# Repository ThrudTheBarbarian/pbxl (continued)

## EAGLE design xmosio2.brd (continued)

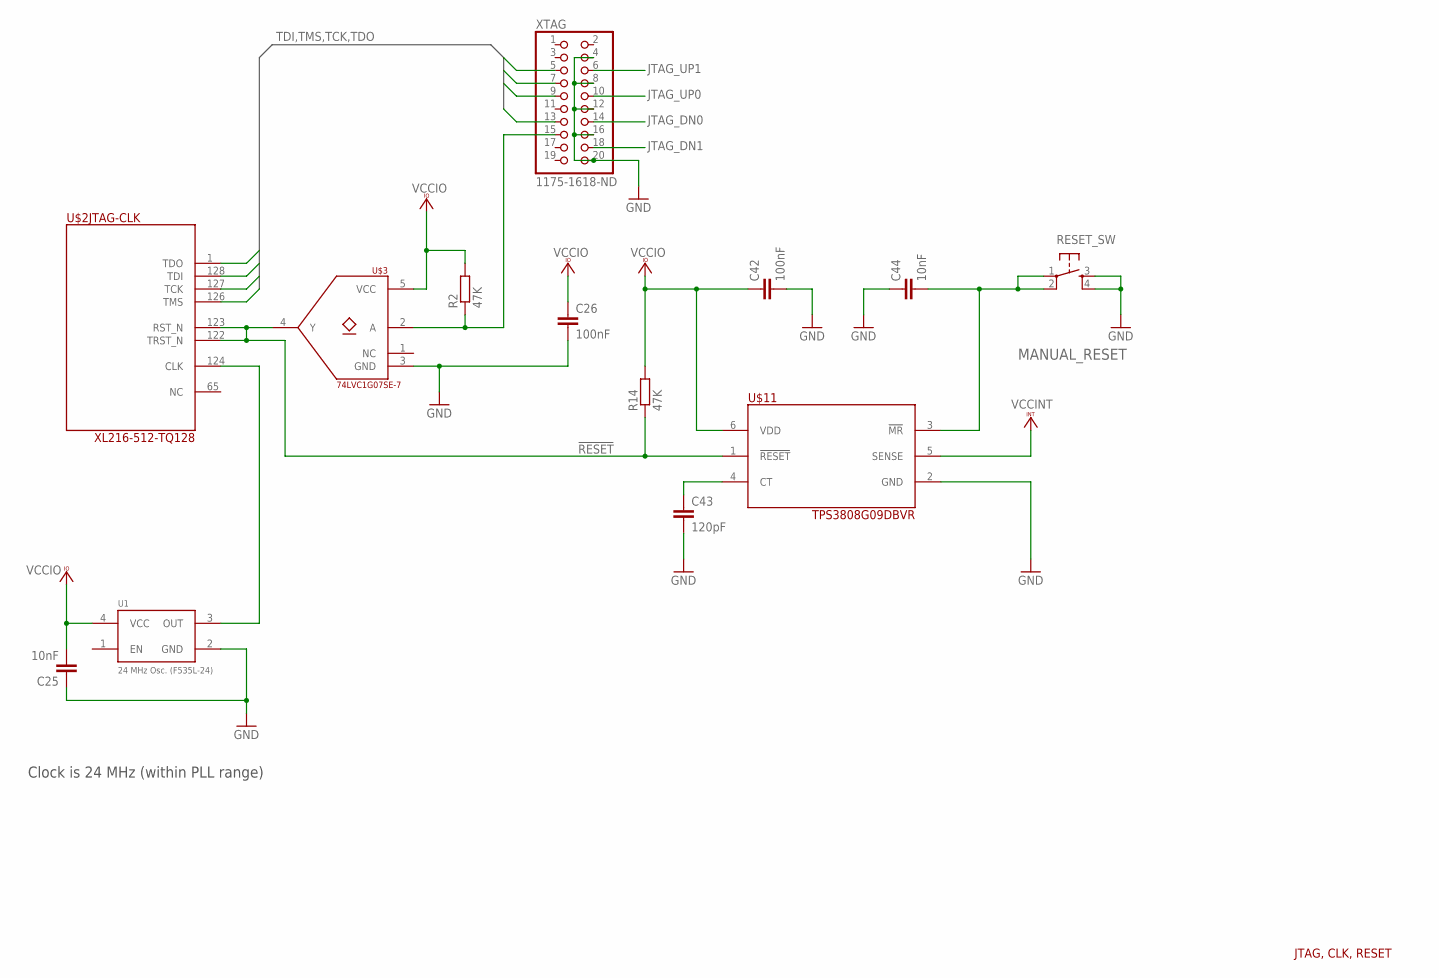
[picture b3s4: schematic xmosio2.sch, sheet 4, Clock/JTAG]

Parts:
C25, C44: 10nF; C0603
C26, C42: 100nF; C0603
C43: 120pF; C0603
R2, R14: 47K; R0603
RESET_SW: MANUAL_RESET; TACTILE-PTH
U1: 24 MHz Osc. (F535L-24); CRYSTAL-OSC-SMD-5X3
U$2: XL216-512-TQ128; TQFP128
U$3: 74LVC1G07SE-7; SOT23-5
U$11: TPS3808G09DBVR; SOT23-6
XTAG: 1175-1618-ND; 2X10/90

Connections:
!RESET!: R14.1, U$2.122 (TRST_N), U$2.123 (RST_N), U$3.4 (Y), U$11.1 (!RESET!)
GND: C25.1, C26.2, C42.2, C43.2, C44.1, RESET_SW.3, RESET_SW.4, U1.2 (GND), U$3.3 (GND), U$11.2 (GND), XTAG.4, XTAG.8, XTAG.12, XTAG.16, XTAG.20; also elsewhere on the board
JTAG_DN0: XTAG.14; also elsewhere on the board
JTAG_DN1: XTAG.18; also elsewhere on the board
JTAG_UP0: XTAG.10; also elsewhere on the board
JTAG_UP1: XTAG.6; also elsewhere on the board
unnamed: U1.3 (OUT), U$2.124 (CLK)
unnamed: R2.1, U$3.2 (A), XTAG.15
unnamed: C43.1, U$11.4 (CT)
unnamed: C44.2, RESET_SW.1, RESET_SW.2, U$11.3 (!MR!)
TCK: U$2.127 (TCK), XTAG.9
TDI: U$2.128 (TDI), XTAG.5
TDO: U$2.1 (TDO), XTAG.13
TMS: U$2.126 (TMS), XTAG.7
VCCINT: U$11.5 (SENSE); also elsewhere on the board
VCCIO: C25.2, C26.1, C42.1, R2.2, R14.2, U1.4 (VCC), U$3.5 (VCC), U$11.6 (VDD); also elsewhere on the board

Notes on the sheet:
JTAG, CLK, RESET
Clock is 24 MHz (within PLL range)

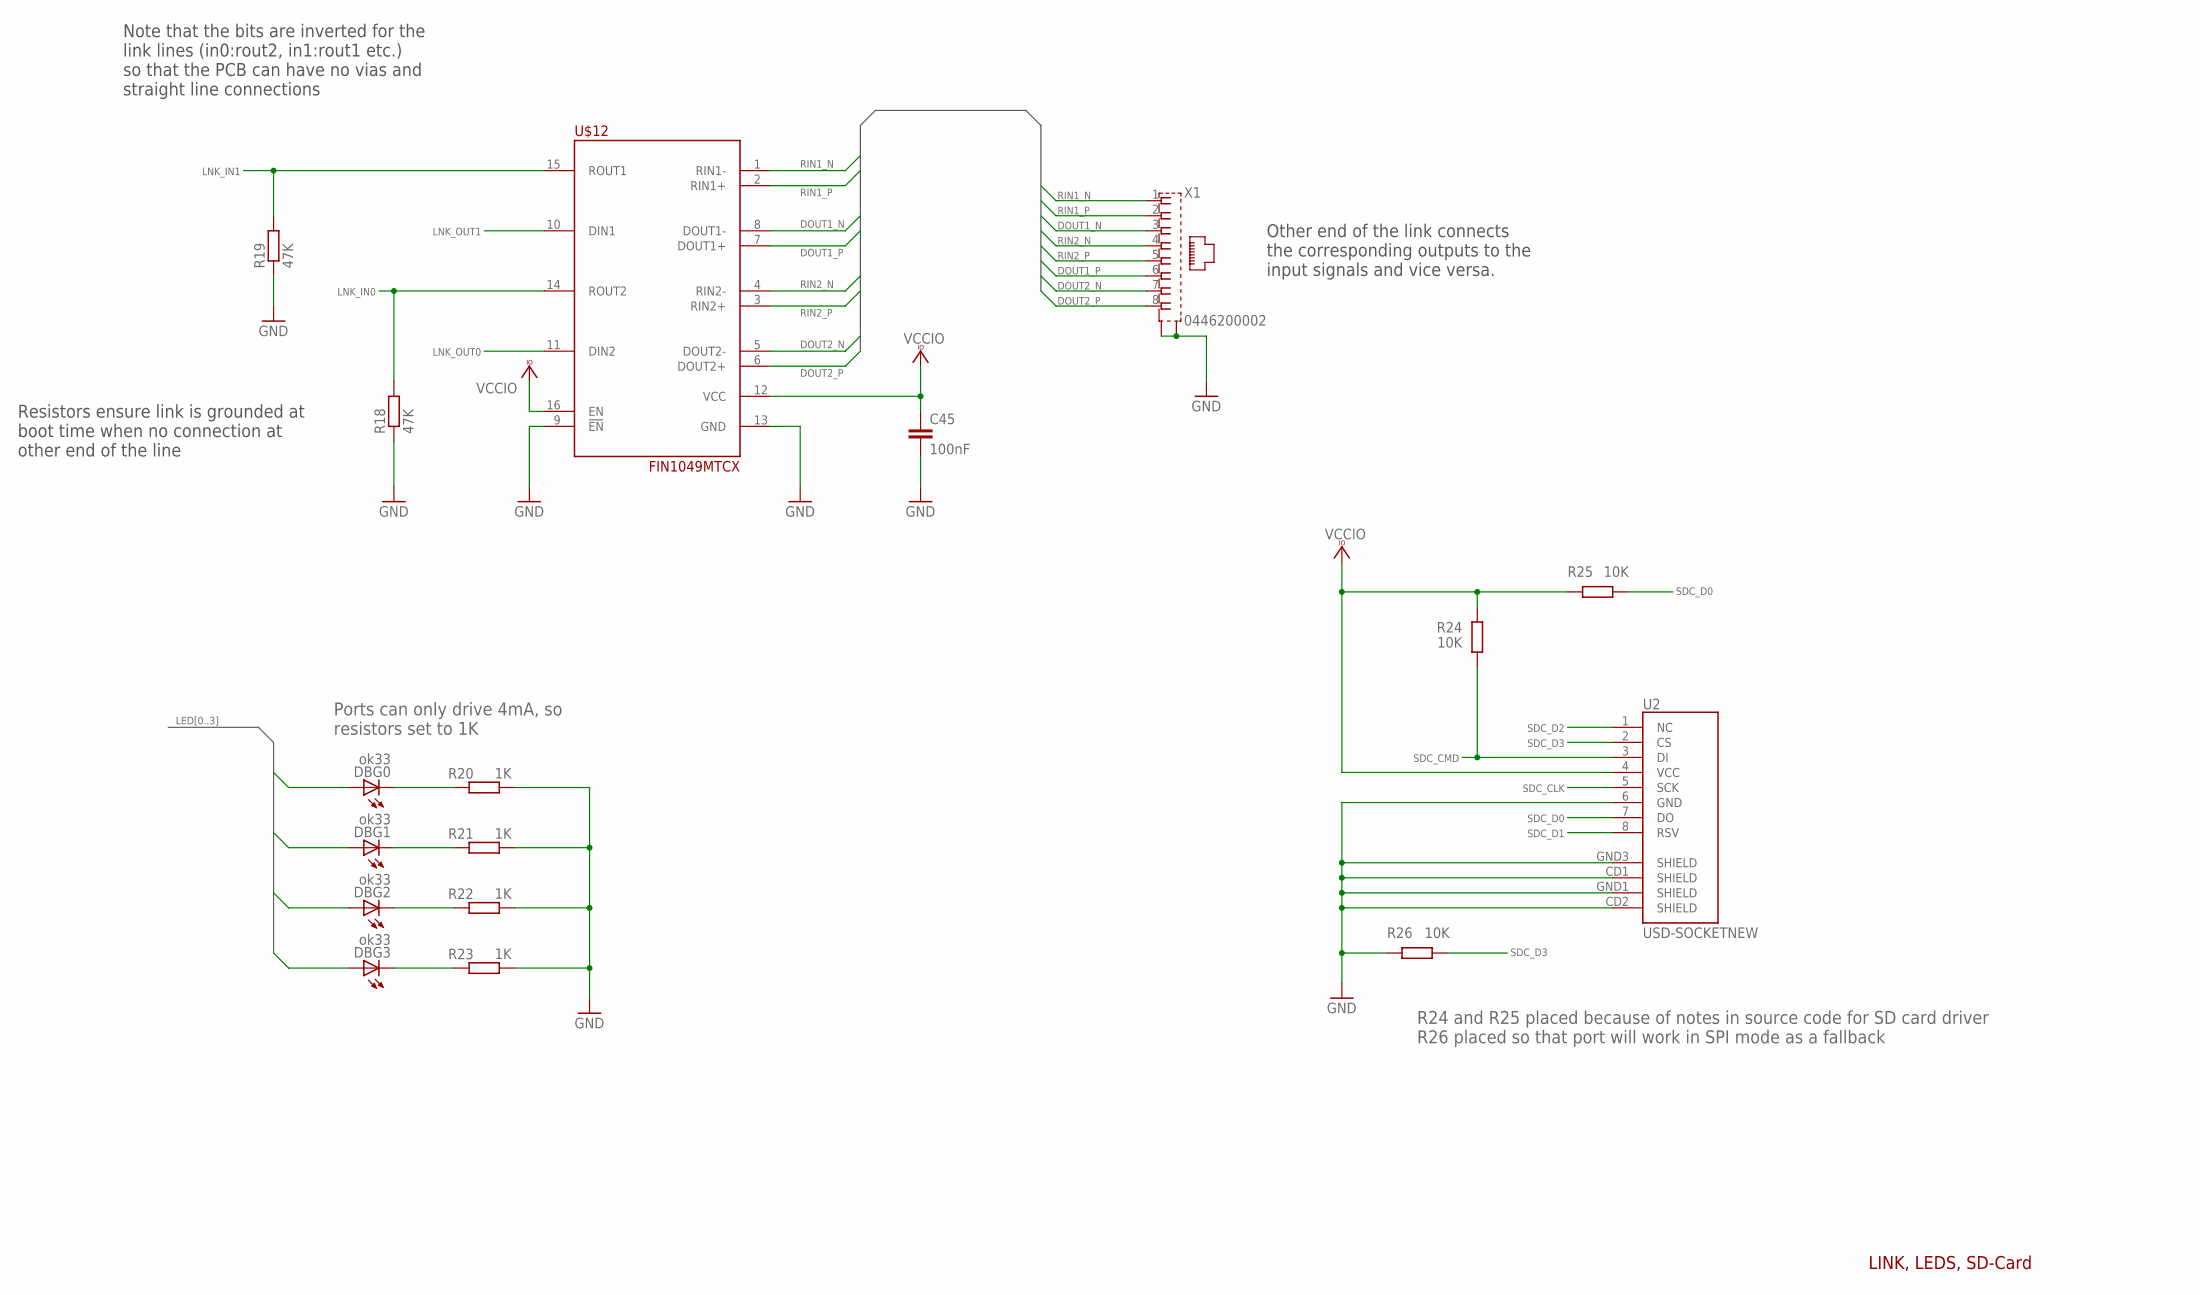
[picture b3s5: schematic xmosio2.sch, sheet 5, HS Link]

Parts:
C45: 100nF; C0603
DBG0, DBG1, DBG2, DBG3: ok33; CHIP-LED0805
R18, R19: 47K; R0603
R20, R21, R22, R23: 1K; R0603
R24, R25, R26: 10K; R0603
U2: USD-SOCKETNEW; MICRO-SD-SOCKET-PP
U$12: FIN1049MTCX; TSSOP16
X1: 0446200002

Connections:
DOUT1_N: U$12.8 (DOUT1-), X1.3
DOUT1_P: U$12.7 (DOUT1+), X1.6
DOUT2_N: U$12.5 (DOUT2-), X1.7
DOUT2_P: U$12.6 (DOUT2+), X1.8
GND: C45.2, R18.1, R19.1, R20.2, R21.2, R22.2, R23.2, R26.2, U2.6 (GND), U2.CD1 (SHIELD), U2.CD2 (SHIELD), U2.GND1 (SHIELD), U2.GND3 (SHIELD), U$12.9 (!EN!), U$12.13 (GND), X1.S@1 (S1), X1.S@2 (S2); also elsewhere on the board
LED0: DBG0.A; also elsewhere on the board
LED1: DBG1.A; also elsewhere on the board
LED2: DBG2.A; also elsewhere on the board
LED3: DBG3.A; also elsewhere on the board
LNK_IN0: R18.2, U$12.14 (ROUT2); also elsewhere on the board
LNK_IN1: R19.2, U$12.15 (ROUT1); also elsewhere on the board
LNK_OUT0: U$12.11 (DIN2); also elsewhere on the board
LNK_OUT1: U$12.10 (DIN1); also elsewhere on the board
unnamed: DBG3.C, R23.1
unnamed: DBG2.C, R22.1
unnamed: DBG1.C, R21.1
unnamed: DBG0.C, R20.1
RIN1_N: U$12.1 (RIN1-), X1.1
RIN1_P: U$12.2 (RIN1+), X1.2
RIN2_N: U$12.4 (RIN2-), X1.4
RIN2_P: U$12.3 (RIN2+), X1.5
SDC_CLK: U2.5 (SCK); also elsewhere on the board
SDC_CMD: R24.1, U2.3 (DI); also elsewhere on the board
SDC_D0: R25.1, U2.7 (DO); also elsewhere on the board
SDC_D1: U2.8 (RSV); also elsewhere on the board
SDC_D2: U2.1 (NC); also elsewhere on the board
SDC_D3: R26.1, U2.2 (CS); also elsewhere on the board
VCCIO: C45.1, R24.2, R25.2, U2.4 (VCC), U$12.12 (VCC), U$12.16 (EN); also elsewhere on the board

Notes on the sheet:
Resistors ensure link is grounded at boot time when no connection at other end of the line
Note that the bits are inverted for the link lines (in0:rout2, in1:rout1 etc.) so that the PCB can have no vias and straight line connections
Other end of the link connects the corresponding outputs to the input signals and vice versa.
LINK, LEDS, SD-Card
Ports can only drive 4mA, so resistors set to 1K
R24 and R25 placed because of notes in source code for SD card driver R26 placed so that port will work in SPI mode as a fallback

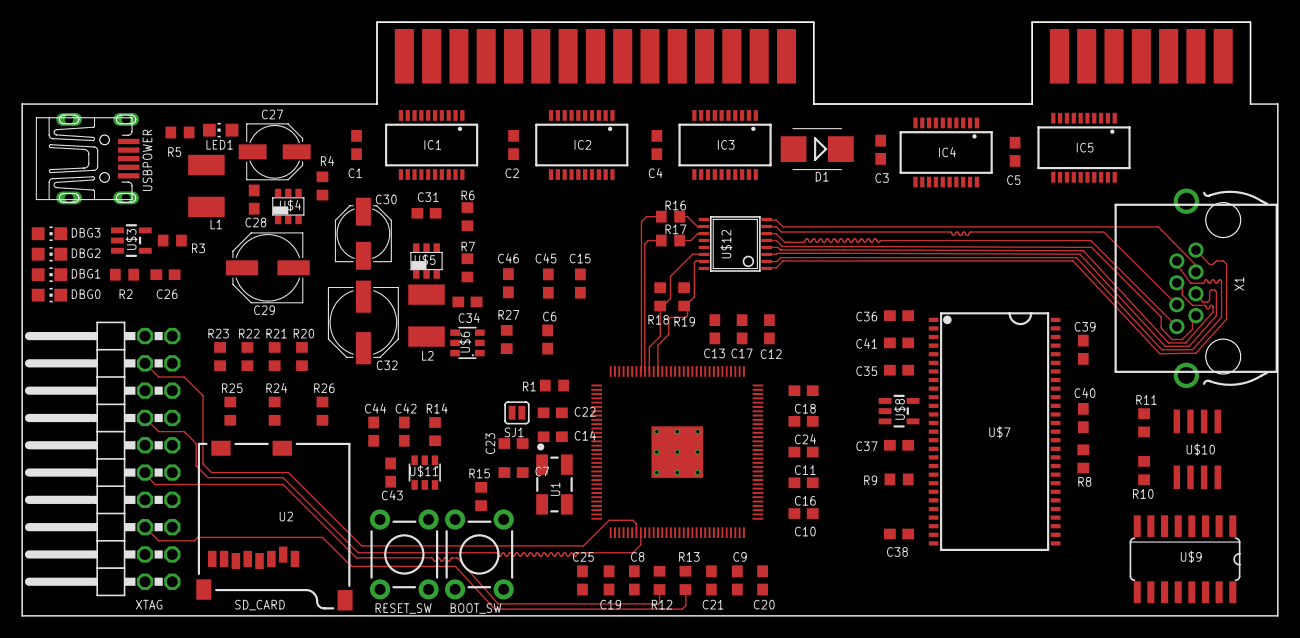
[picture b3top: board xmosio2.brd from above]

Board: 4 copper layers, 116.8 x 55.2 mm, 105 parts (0 on the bottom side), 170 nets.
